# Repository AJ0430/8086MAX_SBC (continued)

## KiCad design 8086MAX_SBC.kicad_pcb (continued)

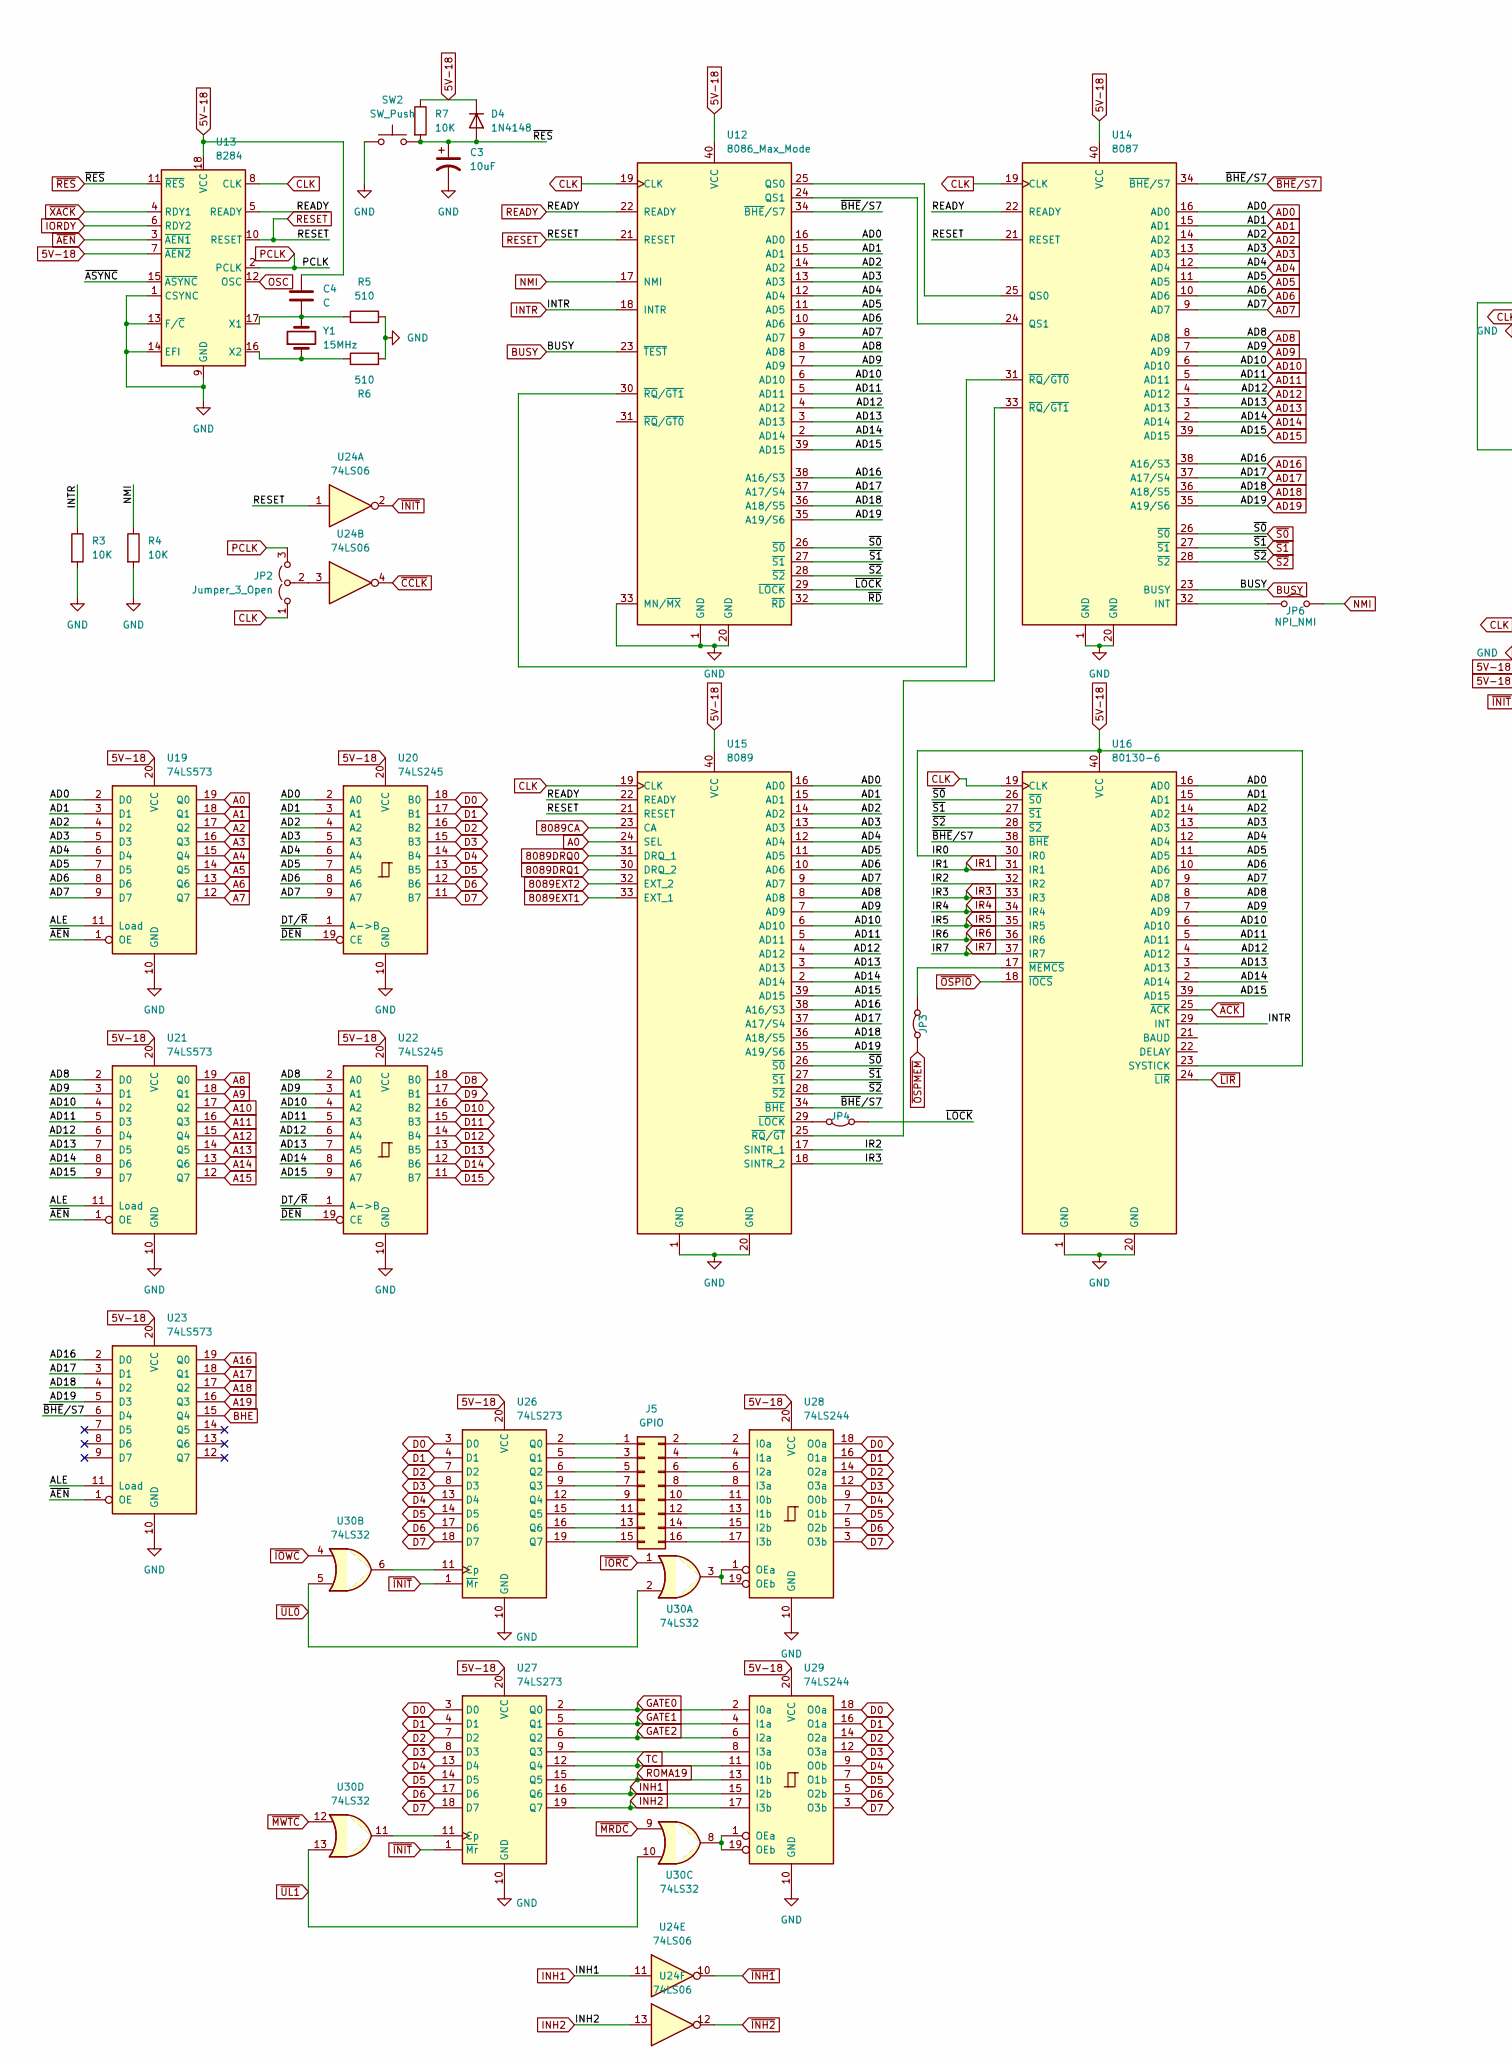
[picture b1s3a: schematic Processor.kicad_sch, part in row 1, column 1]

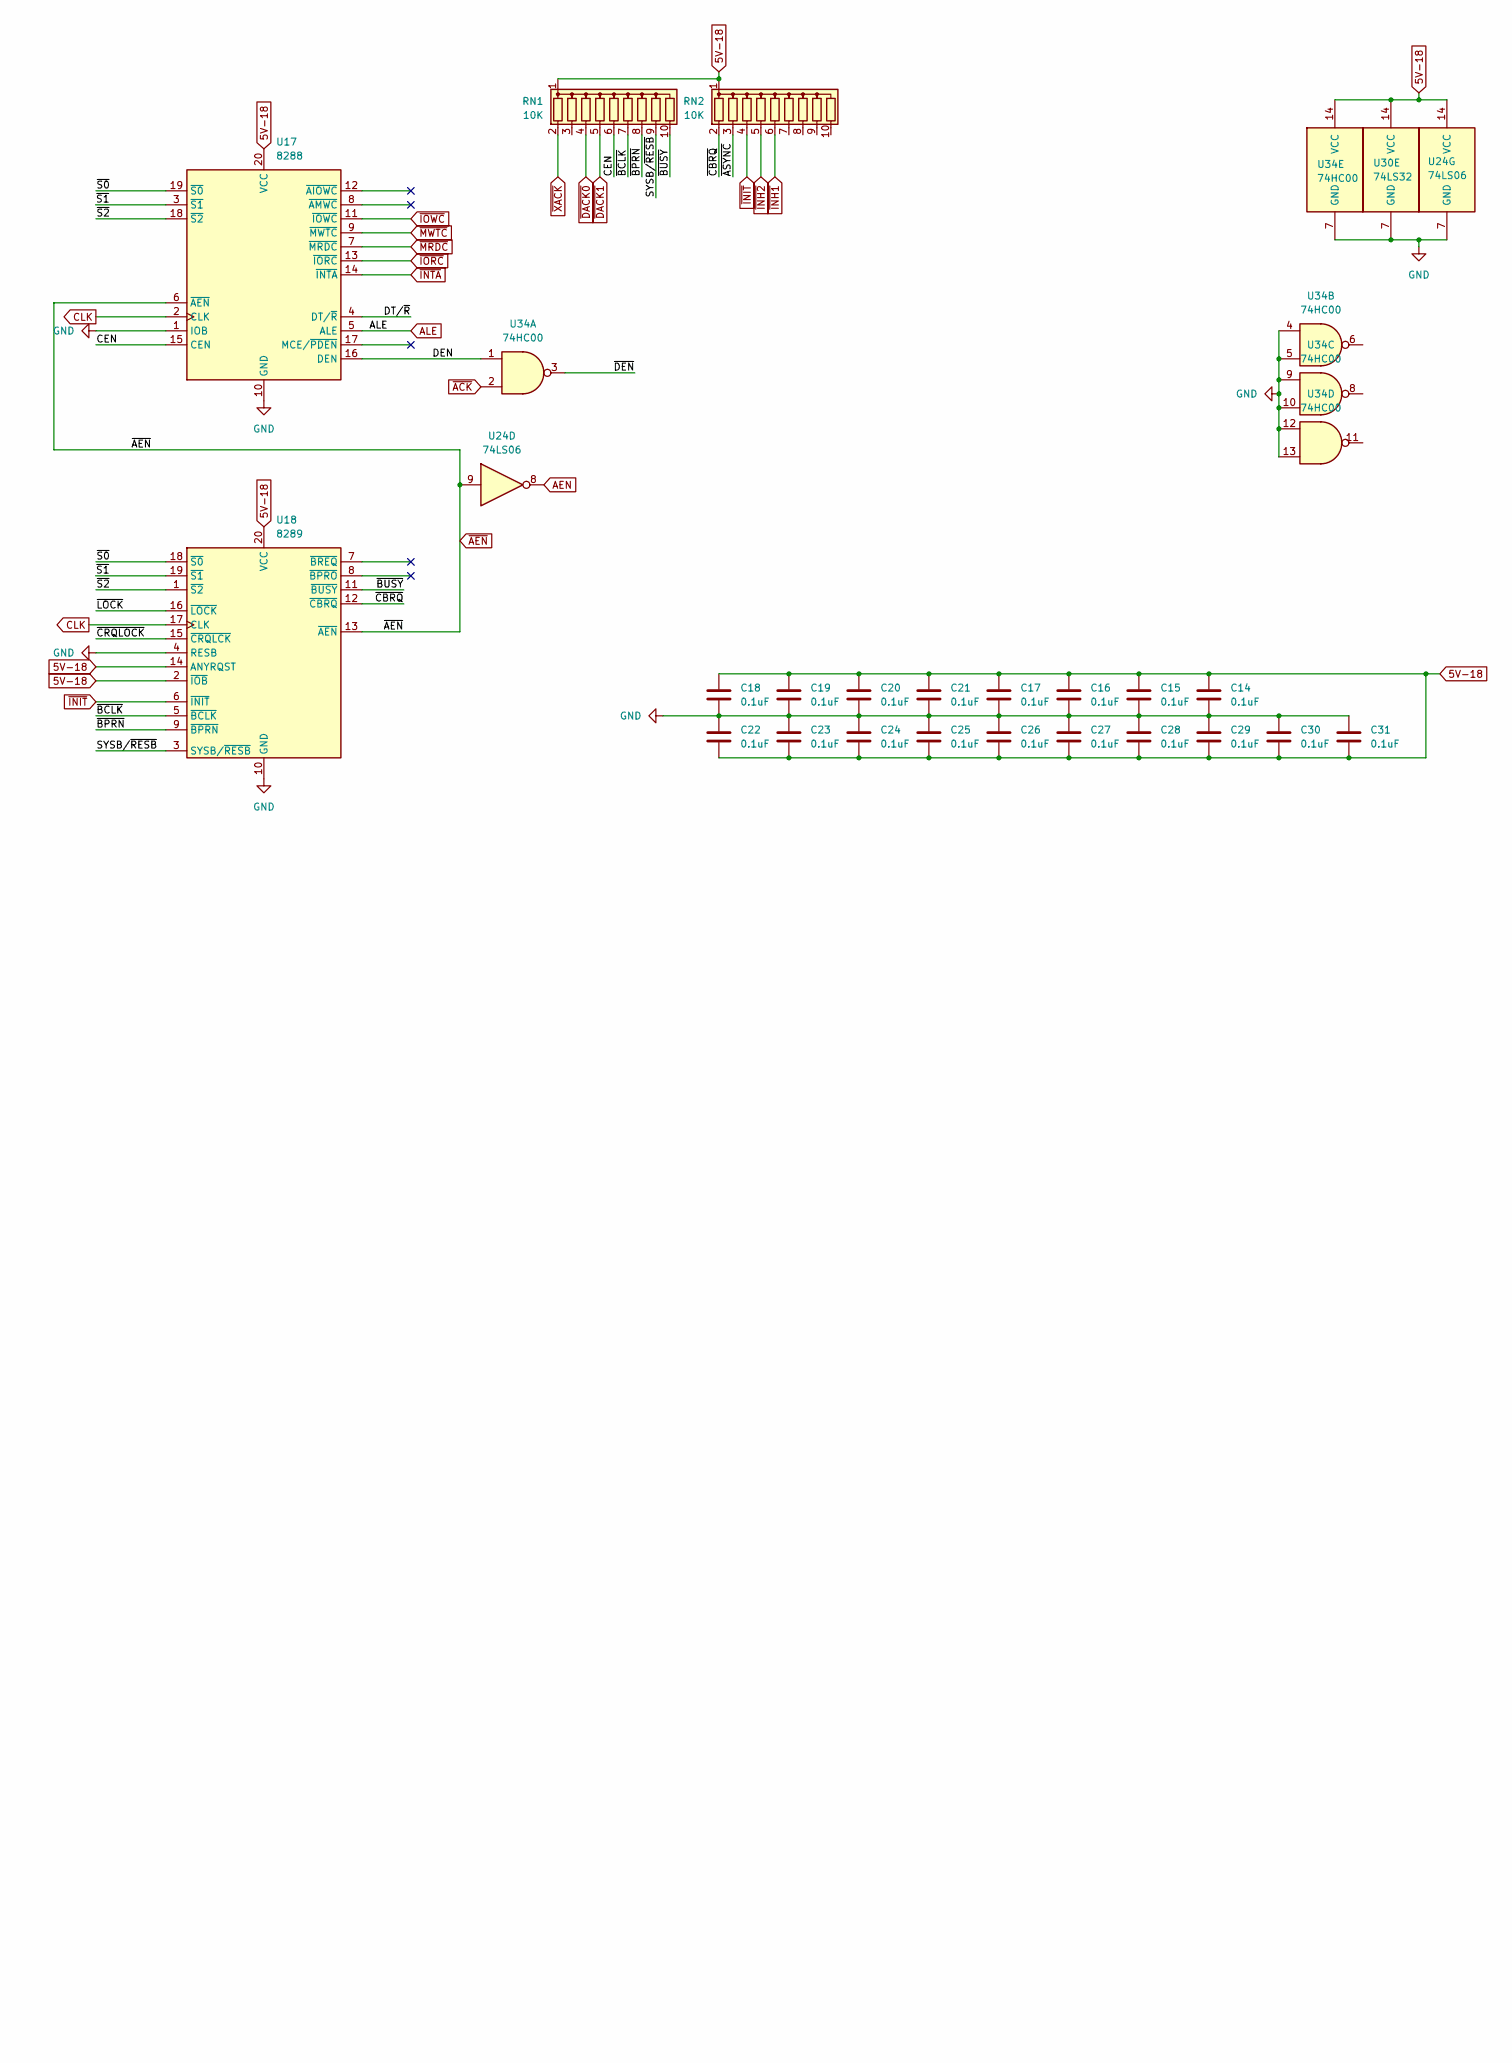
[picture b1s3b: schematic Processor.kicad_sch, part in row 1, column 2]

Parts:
C3: 10uF; CP_Radial_D6.3mm_P2.50mm
C4: C; C_Disc_D8.0mm_W2.5mm_P5.00mm
C14, C15, C16, C17, C18, C19, C20, C21, C22, C23, C24, C25, C26, C27, C28, C29, C30, C31: 0.1uF; C_Disc_D8.0mm_W2.5mm_P5.00mm
D4: 1N4148; D_DO-35_SOD27_P7.62mm_Horizontal
J5: GPIO; PinHeader_2x08_P2.54mm_Vertical
JP2: Jumper_3_Open; PinHeader_1x03_P2.54mm_Vertical
JP3, JP4: PinHeader_1x02_P2.54mm_Vertical
JP6: NPI_NMI; PinHeader_1x02_P2.54mm_Vertical
R3, R4, R7: 10K; R_Axial_DIN0207_L6.3mm_D2.5mm_P7.62mm_Horizontal
R5, R6: 510; R_Axial_DIN0207_L6.3mm_D2.5mm_P7.62mm_Horizontal
RN1, RN2: 10K; R_Array_SIP10
SW2: SW_Push; SW_PUSH_6mm
U12: 8086_Max_Mode; DIP-40_W15.24mm
U13: 8284; DIP-18_W7.62mm
U14: 8087; DIP-40_W15.24mm
U15: 8089; DIP-40_W15.24mm
U16: 80130-6; DIP-40_W15.24mm_Socket
U17: 8288; DIP-20_W7.62mm
U18: 8289; DIP-20_W7.62mm
U19, U21, U23: 74LS573; DIP-20_W7.62mm
U20, U22: 74LS245; DIP-20_W7.62mm
U24: 74LS06; DIP-14_W7.62mm
U26, U27: 74LS273; DIP-20_W7.62mm
U28, U29: 74LS244; DIP-20_W7.62mm
U30: 74LS32; DIP-14_W7.62mm
U34: 74HC00; DIP-14_W7.62mm
Y1: 15MHz; Crystal_HC49-U_Vertical

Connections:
5V-18: C4.1, C14.1, C15.1, C16.1, C17.1, C18.1, C19.1, C20.1, C21.1, C22.2, C23.2, C24.2, C25.2, C26.2, C27.2, C28.2, C29.2, C30.2, C31.2, D4.1 (K), R7.1, RN1.1 (common), RN2.1 (common), U12.40 (VCC), U13.7 (~AEN2), U13.18 (VCC), U14.40 (VCC), U15.40 (VCC), U16.23 (SYSTICK), U16.30 (IR0), U16.40 (VCC), U17.20 (VCC), U18.2 (~IOB), U18.14 (ANYRQST), U18.20 (VCC), U19.20 (VCC), U20.20 (VCC), U21.20 (VCC), U22.20 (VCC), U23.20 (VCC), U24.14 (VCC), U26.20 (VCC), U27.20 (VCC), U28.20 (VCC), U29.20 (VCC), U30.14 (VCC), U34.14 (VCC); also elsewhere on the board
8089CA: U15.23 (CA); also elsewhere on the board
8089DRQ0: U15.31 (DRQ_1); also elsewhere on the board
8089DRQ1: U15.30 (DRQ_2); also elsewhere on the board
8089EXT1: U15.33 (EXT_1); also elsewhere on the board
8089EXT2: U15.32 (EXT_2); also elsewhere on the board
/Processor/CEN: RN1.6 (R5), U17.15 (CEN)
/Processor/DEN: U17.16 (DEN), U34.1
/Processor/DT/~R: U17.4 (DT/~R), U20.1 (A->B), U22.1 (A->B)
/Processor/IR2: U15.17 (SINTR_1), U16.32 (IR2)
/Processor/SYSB/~RESB: RN1.9 (R8), U18.3 (SYSB/~RESB)
/Processor/~ASYNC: RN2.3 (R2), U13.15 (~ASYNC)
/Processor/~BCLK: RN1.7 (R6), U18.5 (~BCLK)
/Processor/~BPRN: RN1.8 (R7), U18.9 (~BPRN)
/Processor/~BUSY: RN1.10 (R9), U18.11 (~BUSY)
/Processor/~CBRQ: RN2.2 (R1), U18.12 (~CBRQ)
/Processor/~CRQLOCK: U18.15 (~CRQLCK)
/Processor/~DEN: U20.19 (CE), U22.19 (CE), U34.3
/Processor/~LOCK: JP4.1 (A), U12.29 (~LOCK), U18.16 (~LOCK)
/Processor/~RD: U12.32 (~RD)
A0: U15.24 (SEL), U19.19 (Q0); also elsewhere on the board
A1: U19.18 (Q1); also elsewhere on the board
A2: U19.17 (Q2); also elsewhere on the board
A3: U19.16 (Q3); also elsewhere on the board
A4: U19.15 (Q4); also elsewhere on the board
A5: U19.14 (Q5); also elsewhere on the board
A6: U19.13 (Q6); also elsewhere on the board
A7: U19.12 (Q7); also elsewhere on the board
A8: U21.19 (Q0); also elsewhere on the board
A9: U21.18 (Q1); also elsewhere on the board
A10: U21.17 (Q2); also elsewhere on the board
A11: U21.16 (Q3); also elsewhere on the board
A12: U21.15 (Q4); also elsewhere on the board
A13: U21.14 (Q5); also elsewhere on the board
A14: U21.13 (Q6); also elsewhere on the board
A15: U21.12 (Q7); also elsewhere on the board
A16: U23.19 (Q0); also elsewhere on the board
A17: U23.18 (Q1); also elsewhere on the board
A18: U23.17 (Q2); also elsewhere on the board
A19: U23.16 (Q3); also elsewhere on the board
AD0: U12.16 (AD0), U14.16 (AD0), U15.16 (AD0), U16.16 (AD0), U19.2 (D0), U20.2 (A0)
AD1: U12.15 (AD1), U14.15 (AD1), U15.15 (AD1), U16.15 (AD1), U19.3 (D1), U20.3 (A1)
AD2: U12.14 (AD2), U14.14 (AD2), U15.14 (AD2), U16.14 (AD2), U19.4 (D2), U20.4 (A2)
AD3: U12.13 (AD3), U14.13 (AD3), U15.13 (AD3), U16.13 (AD3), U19.5 (D3), U20.5 (A3)
AD4: U12.12 (AD4), U14.12 (AD4), U15.12 (AD4), U16.12 (AD4), U19.6 (D4), U20.6 (A4)
AD5: U12.11 (AD5), U14.11 (AD5), U15.11 (AD5), U16.11 (AD5), U19.7 (D5), U20.7 (A5)
AD6: U12.10 (AD6), U14.10 (AD6), U15.10 (AD6), U16.10 (AD6), U19.8 (D6), U20.8 (A6)
AD7: U12.9 (AD7), U14.9 (AD7), U15.9 (AD7), U16.9 (AD7), U19.9 (D7), U20.9 (A7)
AD8: U12.8 (AD8), U14.8 (AD8), U15.8 (AD8), U16.8 (AD8), U21.2 (D0), U22.2 (A0)
AD9: U12.7 (AD9), U14.7 (AD9), U15.7 (AD9), U16.7 (AD9), U21.3 (D1), U22.3 (A1)
AD10: U12.6 (AD10), U14.6 (AD10), U15.6 (AD10), U16.6 (AD10), U21.4 (D2), U22.4 (A2)
AD11: U12.5 (AD11), U14.5 (AD11), U15.5 (AD11), U16.5 (AD11), U21.5 (D3), U22.5 (A3)
AD12: U12.4 (AD12), U14.4 (AD12), U15.4 (AD12), U16.4 (AD12), U21.6 (D4), U22.6 (A4)
AD13: U12.3 (AD13), U14.3 (AD13), U15.3 (AD13), U16.3 (AD13), U21.7 (D5), U22.7 (A5)
AD14: U12.2 (AD14), U14.2 (AD14), U15.2 (AD14), U16.2 (AD14), U21.8 (D6), U22.8 (A6)
AD15: U12.39 (AD15), U14.39 (AD15), U15.39 (AD15), U16.39 (AD15), U21.9 (D7), U22.9 (A7)
AD16: U12.38 (A16/S3), U14.38 (A16/S3), U15.38 (A16/S3), U23.2 (D0)
AD17: U12.37 (A17/S4), U14.37 (A17/S4), U15.37 (A17/S4), U23.3 (D1)
AD18: U12.36 (A18/S5), U14.36 (A18/S5), U15.36 (A18/S5), U23.4 (D2)
AD19: U12.35 (A19/S6), U14.35 (A19/S6), U15.35 (A19/S6), U23.5 (D3)
AEN: U24.8; also elsewhere on the board
ALE: U17.5 (ALE), U19.11 (Load), U21.11 (Load), U23.11 (Load); also elsewhere on the board
BHE: U23.15 (Q4); also elsewhere on the board
BUSY: U12.23 (~TEST), U14.23 (BUSY)
CLK: JP2.1 (A), U12.19 (CLK), U13.8 (CLK), U14.19 (CLK), U15.19 (CLK), U16.19 (CLK), U17.2 (CLK), U18.17 (CLK); also elsewhere on the board
D0: U20.18 (B0), U26.3 (D0), U27.3 (D0), U28.18 (O0a), U29.18 (O0a); also elsewhere on the board
D1: U20.17 (B1), U26.4 (D1), U27.4 (D1), U28.16 (O1a), U29.16 (O1a); also elsewhere on the board
D2: U20.16 (B2), U26.7 (D2), U27.7 (D2), U28.14 (O2a), U29.14 (O2a); also elsewhere on the board
D3: U20.15 (B3), U26.8 (D3), U27.8 (D3), U28.12 (O3a), U29.12 (O3a); also elsewhere on the board
D4: U20.14 (B4), U26.13 (D4), U27.13 (D4), U28.9 (O0b), U29.9 (O0b); also elsewhere on the board
D5: U20.13 (B5), U26.14 (D5), U27.14 (D5), U28.7 (O1b), U29.7 (O1b); also elsewhere on the board
D6: U20.12 (B6), U26.17 (D6), U27.17 (D6), U28.5 (O2b), U29.5 (O2b); also elsewhere on the board
D7: U20.11 (B7), U26.18 (D7), U27.18 (D7), U28.3 (O3b), U29.3 (O3b); also elsewhere on the board
D8: U22.18 (B0); also elsewhere on the board
D9: U22.17 (B1); also elsewhere on the board
D10: U22.16 (B2); also elsewhere on the board
D11: U22.15 (B3); also elsewhere on the board
D12: U22.14 (B4); also elsewhere on the board
D13: U22.13 (B5); also elsewhere on the board
D14: U22.12 (B6); also elsewhere on the board
D15: U22.11 (B7); also elsewhere on the board
GATE0: U27.2 (Q0), U29.2 (I0a)
GATE1: U27.5 (Q1), U29.4 (I1a)
GATE2: U27.6 (Q2), U29.6 (I2a)
GND: C3.2, C14.2, C15.2, C16.2, C17.2, C18.2, C19.2, C20.2, C21.2, C22.1, C23.1, C24.1, C25.1, C26.1, C27.1, C28.1, C29.1, C30.1, C31.1, R3.2, R4.2, R5.2, R6.2, SW2.1, U12.1 (GND), U12.20 (GND), U12.33 (MN/~MX), U13.1 (CSYNC), U13.9 (GND), U13.13 (F/~C), U13.14 (EFI), U14.1 (GND), U14.20 (GND), U15.1 (GND), U15.20 (GND), U16.1 (GND), U16.20 (GND), U17.1 (IOB), U17.10 (GND), U18.4 (RESB), U18.10 (GND), U19.10 (GND), U20.10 (GND), U21.10 (GND), U22.10 (GND), U23.10 (GND), U24.7 (GND), U26.10 (GND), U27.10 (GND), U28.10 (GND), U29.10 (GND), U30.7 (GND), U34.4, U34.5, U34.7 (GND), U34.9, U34.10, U34.12, U34.13; also elsewhere on the board
INH1: U24.11, U27.16 (Q6), U29.15 (I2b)
INH2: U24.13, U27.19 (Q7), U29.17 (I3b)
INTR: R3.1, U12.18 (INTR), U16.29 (INT)
IORDY: U13.6 (RDY2); also elsewhere on the board
IR1: U16.31 (IR1); also elsewhere on the board
IR3: U15.18 (SINTR_2), U16.33 (IR3); also elsewhere on the board
IR4: U16.34 (IR4); also elsewhere on the board
IR5: U16.35 (IR5); also elsewhere on the board
IR6: U16.36 (IR6); also elsewhere on the board
IR7: U16.37 (IR7); also elsewhere on the board
NMI: JP6.2 (B), R4.1, U12.17 (NMI); also elsewhere on the board
unnamed: J5.1, U26.2 (Q0)
unnamed: J5.2, U28.2 (I0a)
unnamed: J5.3, U26.5 (Q1)
unnamed: J5.4, U28.4 (I1a)
unnamed: J5.5, U26.6 (Q2)
unnamed: J5.6, U28.6 (I2a)
unnamed: J5.7, U26.9 (Q3)
unnamed: J5.8, U28.8 (I3a)
unnamed: J5.9, U26.12 (Q4)
unnamed: J5.10, U28.11 (I0b)
unnamed: J5.11, U26.15 (Q5)
unnamed: J5.12, U28.13 (I1b)
unnamed: J5.13, U26.16 (Q6)
unnamed: J5.14, U28.15 (I2b)
unnamed: J5.15, U26.19 (Q7)
unnamed: J5.16, U28.17 (I3b)
unnamed: JP2.2 (C), U24.3
unnamed: JP3.2 (B), U16.17 (~MEMCS)
unnamed: JP4.2 (B), U15.29 (~LOCK)
unnamed: JP6.1 (A), U14.32 (INT)
unnamed: U12.25 (QS0), U14.25 (QS0)
unnamed: U12.24 (QS1), U14.24 (QS1)
unnamed: U12.30 (~RQ/~GT1), U14.31 (~RQ/~GT0)
unnamed: C4.2, R5.1, U13.17 (X1), Y1.2
unnamed: R6.1, U13.16 (X2), Y1.1
unnamed: U14.33 (~RQ/~GT1), U15.25 (~RQ/~GT)
unnamed: U26.11 (Cp), U30.6
unnamed: U27.11 (Cp), U30.11
unnamed: U27.9 (Q3), U29.8 (I3a)
unnamed: U28.1 (OEa), U28.19 (OEb), U30.3
unnamed: U29.1 (OEa), U29.19 (OEb), U30.8
OSC: U13.12 (OSC); also elsewhere on the board
PCLK: JP2.3 (B), U13.2 (PCLK); also elsewhere on the board
READY: U12.22 (READY), U13.5 (READY), U14.22 (READY), U15.22 (READY)
RESET: U12.21 (RESET), U13.10 (RESET), U14.21 (RESET), U15.21 (RESET), U24.1; also elsewhere on the board
ROMA19: U27.15 (Q5), U29.13 (I1b); also elsewhere on the board
TC: U27.12 (Q4), U29.11 (I0b); also elsewhere on the board
~ACK: U16.25 (~ACK), U34.2
~AEN: U13.3 (~AEN1), U17.6 (~AEN), U18.13 (~AEN), U19.1 (OE), U21.1 (OE), U23.1 (OE), U24.9
~BHE/S7: U12.34 (~BHE/S7), U14.34 (~BHE/S7), U15.34 (~BHE), U16.38 (~BHE), U23.6 (D4)
~CCLK: U24.4; also elsewhere on the board
~DACK0: RN1.4 (R3)
~DACK1: RN1.5 (R4)
~INH1: RN2.6 (R5), U24.10; also elsewhere on the board
~INH2: RN2.5 (R4), U24.12; also elsewhere on the board
~INIT: RN2.4 (R3), U18.6 (~INIT), U24.2, U26.1 (~Mr), U27.1 (~Mr)
~INTA: U17.14 (~INTA)
~IORC: U17.13 (~IORC), U30.1; also elsewhere on the board
~IOWC: U17.11 (~IOWC), U30.4; also elsewhere on the board
~LIR: U16.24 (~LIR)
~MRDC: U17.7 (~MRDC), U30.9; also elsewhere on the board
~MWTC: U17.9 (~MWTC), U30.12; also elsewhere on the board
~OSPIO: U16.18 (~IOCS)
~OSPMEM: JP3.1 (A)
~RES: C3.1, D4.2 (A), R7.2, SW2.2, U13.11 (~RES)
~S0: U12.26 (~S0), U14.26 (~S0), U15.26 (~S0), U16.26 (~S0), U17.19 (~S0), U18.18 (~S0)
~S1: U12.27 (~S1), U14.27 (~S1), U15.27 (~S1), U16.27 (~S1), U17.3 (~S1), U18.19 (~S1)
~S2: U12.28 (~S2), U14.28 (~S2), U15.28 (~S2), U16.28 (~S2), U17.18 (~S2), U18.1 (~S2)
~UL0: U30.2, U30.5; also elsewhere on the board
~UL1: U30.10, U30.13; also elsewhere on the board
~XACK: RN1.2 (R1), U13.4 (RDY1); also elsewhere on the board

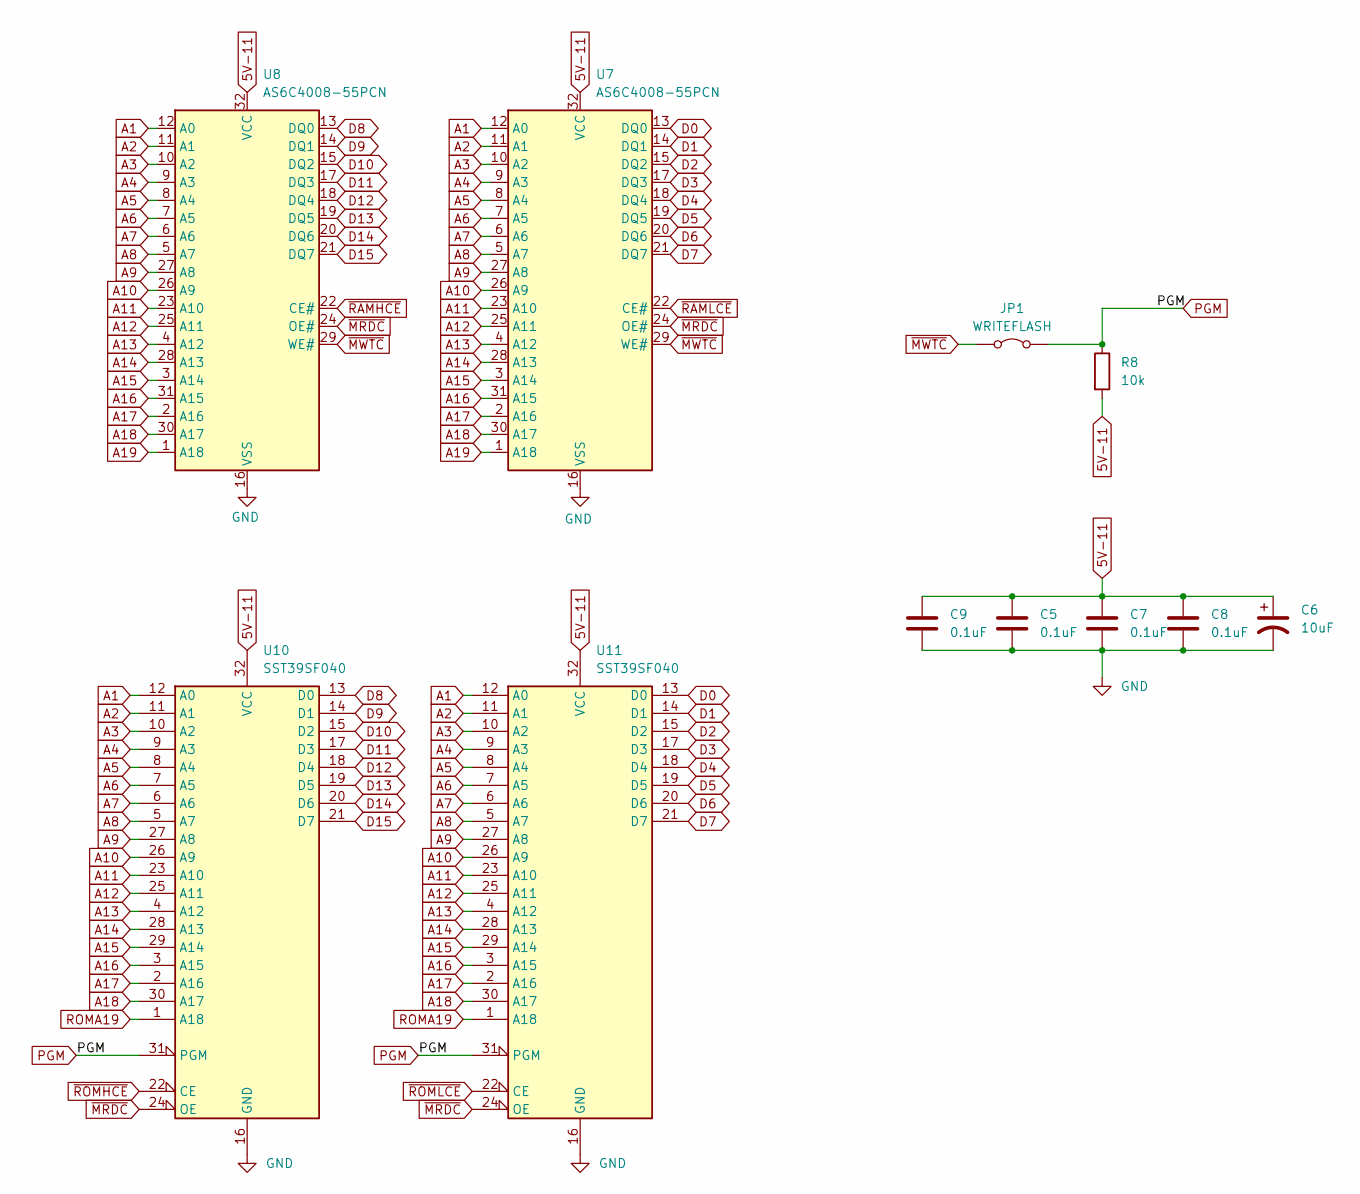
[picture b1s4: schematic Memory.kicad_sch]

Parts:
C5, C7, C8, C9: 0.1uF; C_Disc_D8.0mm_W2.5mm_P5.00mm
C6: 10uF; CP_Radial_D5.0mm_P2.50mm
JP1: WRITEFLASH; PinHeader_1x02_P2.54mm_Vertical
R8: 10k; R_Axial_DIN0207_L6.3mm_D2.5mm_P7.62mm_Horizontal
U7, U8: AS6C4008-55PCN; DIP-32_W15.24mm
U10, U11: SST39SF040; DIP-32_W15.24mm

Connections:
5V-11: C5.1, C6.1, C7.1, C8.1, C9.1, R8.2, U7.32 (VCC), U8.32 (VCC), U10.32 (VCC), U11.32 (VCC); also elsewhere on the board
A1: U7.12 (A0), U8.12 (A0), U10.12 (A0), U11.12 (A0); also elsewhere on the board
A2: U7.11 (A1), U8.11 (A1), U10.11 (A1), U11.11 (A1); also elsewhere on the board
A3: U7.10 (A2), U8.10 (A2), U10.10 (A2), U11.10 (A2); also elsewhere on the board
A4: U7.9 (A3), U8.9 (A3), U10.9 (A3), U11.9 (A3); also elsewhere on the board
A5: U7.8 (A4), U8.8 (A4), U10.8 (A4), U11.8 (A4); also elsewhere on the board
A6: U7.7 (A5), U8.7 (A5), U10.7 (A5), U11.7 (A5); also elsewhere on the board
A7: U7.6 (A6), U8.6 (A6), U10.6 (A6), U11.6 (A6); also elsewhere on the board
A8: U7.5 (A7), U8.5 (A7), U10.5 (A7), U11.5 (A7); also elsewhere on the board
A9: U7.27 (A8), U8.27 (A8), U10.27 (A8), U11.27 (A8); also elsewhere on the board
A10: U7.26 (A9), U8.26 (A9), U10.26 (A9), U11.26 (A9); also elsewhere on the board
A11: U7.23 (A10), U8.23 (A10), U10.23 (A10), U11.23 (A10); also elsewhere on the board
A12: U7.25 (A11), U8.25 (A11), U10.25 (A11), U11.25 (A11); also elsewhere on the board
A13: U7.4 (A12), U8.4 (A12), U10.4 (A12), U11.4 (A12); also elsewhere on the board
A14: U7.28 (A13), U8.28 (A13), U10.28 (A13), U11.28 (A13); also elsewhere on the board
A15: U7.3 (A14), U8.3 (A14), U10.29 (A14), U11.29 (A14); also elsewhere on the board
A16: U7.31 (A15), U8.31 (A15), U10.3 (A15), U11.3 (A15); also elsewhere on the board
A17: U7.2 (A16), U8.2 (A16), U10.2 (A16), U11.2 (A16); also elsewhere on the board
A18: U7.30 (A17), U8.30 (A17), U10.30 (A17), U11.30 (A17); also elsewhere on the board
A19: U7.1 (A18), U8.1 (A18); also elsewhere on the board
D0: U7.13 (DQ0), U11.13 (D0); also elsewhere on the board
D1: U7.14 (DQ1), U11.14 (D1); also elsewhere on the board
D2: U7.15 (DQ2), U11.15 (D2); also elsewhere on the board
D3: U7.17 (DQ3), U11.17 (D3); also elsewhere on the board
D4: U7.18 (DQ4), U11.18 (D4); also elsewhere on the board
D5: U7.19 (DQ5), U11.19 (D5); also elsewhere on the board
D6: U7.20 (DQ6), U11.20 (D6); also elsewhere on the board
D7: U7.21 (DQ7), U11.21 (D7); also elsewhere on the board
D8: U8.13 (DQ0), U10.13 (D0); also elsewhere on the board
D9: U8.14 (DQ1), U10.14 (D1); also elsewhere on the board
D10: U8.15 (DQ2), U10.15 (D2); also elsewhere on the board
D11: U8.17 (DQ3), U10.17 (D3); also elsewhere on the board
D12: U8.18 (DQ4), U10.18 (D4); also elsewhere on the board
D13: U8.19 (DQ5), U10.19 (D5); also elsewhere on the board
D14: U8.20 (DQ6), U10.20 (D6); also elsewhere on the board
D15: U8.21 (DQ7), U10.21 (D7); also elsewhere on the board
GND: C5.2, C6.2, C7.2, C8.2, C9.2, U7.16 (VSS), U8.16 (VSS), U10.16 (GND), U11.16 (GND); also elsewhere on the board
PGM: JP1.2 (B), R8.1, U10.31 (PGM), U11.31 (PGM)
ROMA19: U10.1 (A18), U11.1 (A18); also elsewhere on the board
~MRDC: U7.24 (OE#), U8.24 (OE#), U10.24 (OE), U11.24 (OE); also elsewhere on the board
~MWTC: JP1.1 (A), U7.29 (WE#), U8.29 (WE#); also elsewhere on the board
~RAMHCE: U8.22 (CE#); also elsewhere on the board
~RAMLCE: U7.22 (CE#); also elsewhere on the board
~ROMHCE: U10.22 (CE); also elsewhere on the board
~ROMLCE: U11.22 (CE); also elsewhere on the board

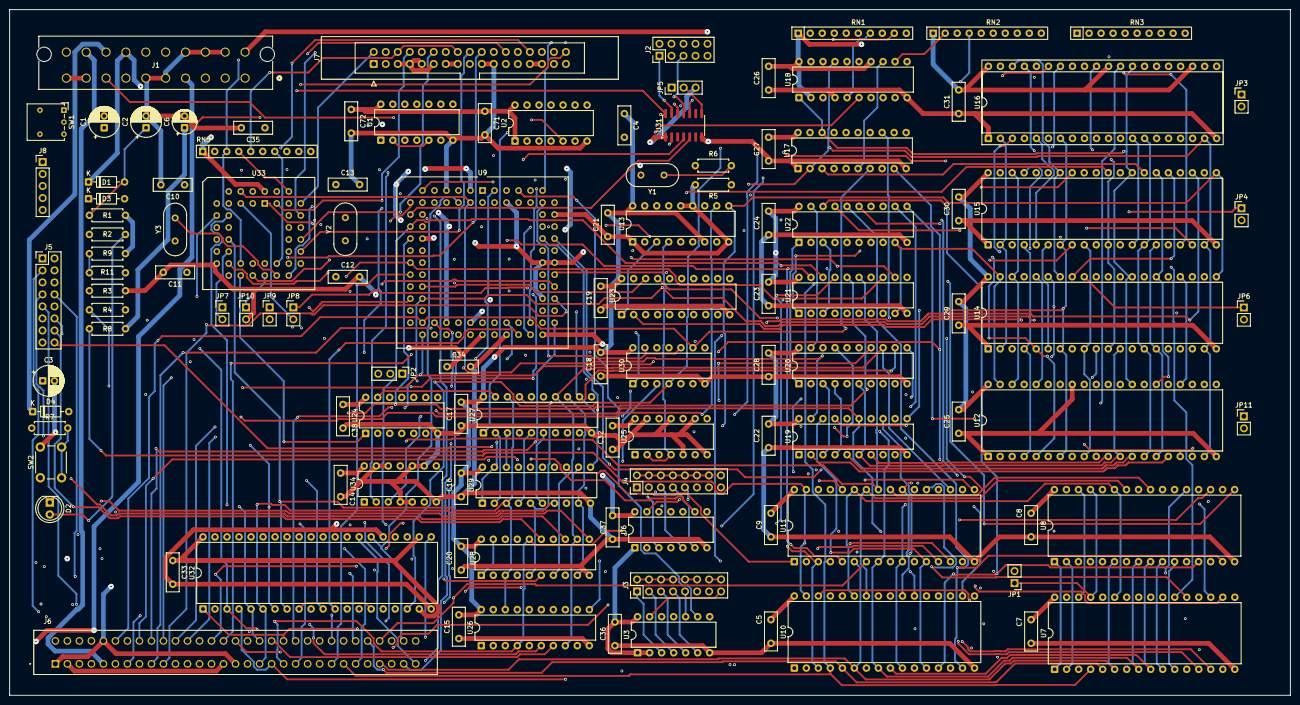
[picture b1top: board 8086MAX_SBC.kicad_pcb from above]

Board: 4 copper layers, 270.8 x 145.0 mm, 114 parts (0 on the bottom side), 240 nets.

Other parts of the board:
C38: 0.1uF; C_Disc_D8.0mm_W2.5mm_P5.00mm
RN3: 10K; R_Array_SIP10

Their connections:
5V-18: C38.1, RN3.1 (common); also elsewhere on the board
GND: C38.2; also elsewhere on the board

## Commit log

2025-11-25 Actually Committing Files
2026-01-28 Adjusted Data Bus for 80130
2026-03-16 assigned all footprints
2026-03-17 Updated PCB
2026-03-17 Fixed some silkscreen overlap
2026-03-18 Fixed missing nets
2026-03-18 Minor changes to ground
2026-03-18 Removed redundant schematic from project
2026-03-28 Finished routing traces
